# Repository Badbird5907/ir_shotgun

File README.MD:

# IR Shotgun
This is a IR shotgun (blaster) for the flipper zero that uses 8x APTD3216F3C-P22 infrared LEDs to absolutely FLOOD a room with infrared light.

## How does it work?
The flipper zero drives the A7 pin with PWM, which in turn drives the AO3400A MOSFET. The MOSFET then turns on and off the IR LEDs.

## How does this compare to the Rabbit Labs IR Blaster?
This blaster is (I think) a bit more powerful, and more directional compared to the Rabbit Labs IR Blaster.

## Design choices
- Instead of using 1x3 pin headers, I used 2x3 headers to provide better structural support for the blaster PCB.
- I used the AO3400A MOSFET over the 2N7000 because it's able to handle more current.
- My calculations for the resistor values for the LEDs (70 ohm -> 68 ohm) were based on the DC Forward Current of 50mA and not the peak forward current of 1200mA.

## Pictures

## BOM
|Name                                                                                                                       |Qty   |Price Per (USD)|Total (USD)|Link                                                                                       |
|---------------------------------------------------------------------------------------------------------------------------|------|---------------|-----------|-------------------------------------------------------------------------------------------|
|90 Degree header                                                                                                           |1     |$0.67          |$0.67      |https://www.digikey.ca/en/products/detail/w%C3%BCrth-elektronik/61300621021/4846834        |
|0.1uF 0805 cap                                                                                                             |1     |$0.08          |$0.08      |https://www.digikey.ca/en/products/detail/samsung-electro-mechanics/CL21B104KBCNNNC/3886661|
|10uF 1206 cap                                                                                                              |1     |$0.08          |$0.08      |https://www.digikey.ca/en/products/detail/samsung-electro-mechanics/CL31B106KAHNNNE/3887462|
|IR LED                                                                                                                     |8     |$0.52          |$4.16      |https://www.digikey.ca/en/products/detail/kingbright/APTD3216F3C-P22/8591562               |
|AO3400A MOSFET                                                                                                             |1     |$0.46          |$0.46      |https://www.digikey.ca/en/products/detail/alpha-omega-semiconductor-inc/AO3400A/1855772    |
|68 ohm res                                                                                                                 |4     |$0.60          |$2.40      |https://www.digikey.ca/en/products/detail/susumu/HRG3216P-68R0-D-T1/5762544                |
|10k res                                                                                                                    |1     |$0.10          |$0.10      |https://www.digikey.ca/en/products/detail/stackpole-electronics-inc/RMCF0805FT10K0/1760676 |
|15mm pin headers                                                                                                           |1     |$3.43          |$3.43      |https://www.aliexpress.com/item/1005006783391171.html                                      |
|Blaster PCB (JLC, LeadFree HASL)                                                                                           |1     |$5.20          |$5.20      |                                                                                           |
|Base PCB (JLC, LeadFree HASL)                                                                                              |1     |$5.20          |$5.20      |                                                                                           |
|TOTAL                                                                                                                      |      |               |$21.78     |                                                                                           |
|NOTE: Most of the resistors/caps here cost more in packages of one than in packages of 10+, I'd suggest ordering 10 of each|      |               |           |                                                                                           |
|                                                                                                                           |      |               |           |                                                                                           |
|                                                                                                                           |USD   |               |           |                                                                                           |
|JLC - DHL                                                                                                                  |$17.50|               |           |                                                                                           |
|DigiKey                                                                                                                    |$5.84 |               |           |                                                                                           |
|                                                                                                                           |      |               |           |                                                                                           |
|                                                                                                                           |      |               |           |                                                                                           |
|Grand Total                                                                                                                |      |               |$45.12     |                                                                                           |
                                                                                  |      |               |           |                                                                                           |
|Shipping

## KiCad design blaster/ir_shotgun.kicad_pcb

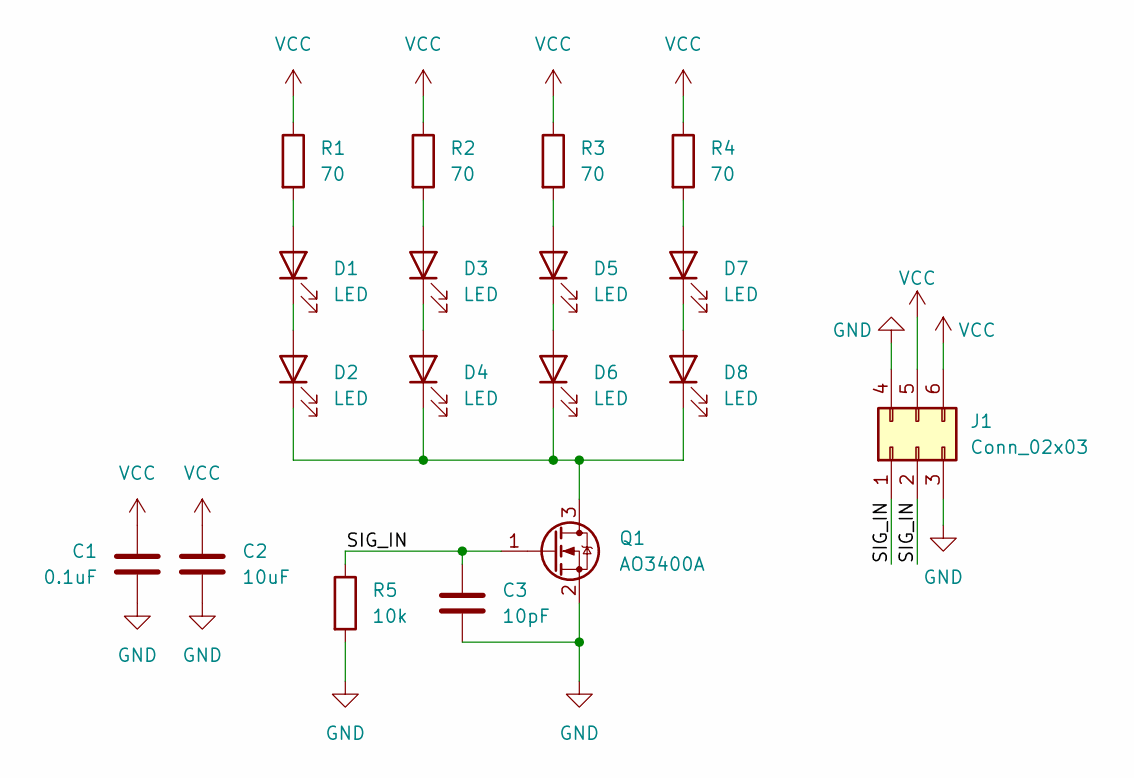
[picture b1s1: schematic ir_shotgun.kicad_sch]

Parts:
C1: 0.1uF; C_0805_2012Metric
C2: 10uF; C_1206_3216Metric
C3: 10pF; C_0805_2012Metric
D1, D2, D3, D4, D5, D6, D7, D8: LED; LED_1206_3216Metric
J1: Conn_02x03; PinHeader_2x03_P2.54mm_Vertical
Q1: AO3400A; SOT-23
R1, R2, R3, R4: 70; LED_1206_3216Metric
R5: 10k; R_0805_2012Metric

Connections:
/SIG_IN: C3.1, J1.1, J1.2, Q1.1 (G), R5.1
GND: C1.2, C2.2, C3.2, J1.3, J1.4, Q1.2 (S), R5.2
unnamed: D1.2 (A), R1.2
unnamed: D1.1 (K), D2.2 (A)
unnamed: D2.1 (K), D4.1 (K), D6.1 (K), D8.1 (K), Q1.3 (D)
unnamed: D3.2 (A), R2.2
unnamed: D3.1 (K), D4.2 (A)
unnamed: D5.2 (A), R3.2
unnamed: D5.1 (K), D6.2 (A)
unnamed: D7.2 (A), R4.2
unnamed: D7.1 (K), D8.2 (A)
VCC: C1.1, C2.1, J1.5, J1.6, R1.1, R2.1, R3.1, R4.1

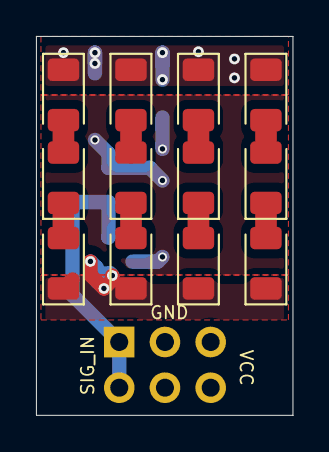
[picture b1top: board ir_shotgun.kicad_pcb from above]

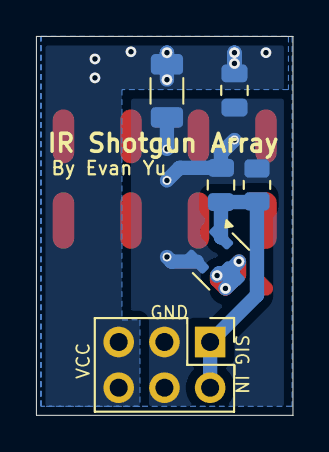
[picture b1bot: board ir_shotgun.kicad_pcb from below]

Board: 2 copper layers, 14.2 x 21.0 mm, 18 parts (6 on the bottom side), 12 nets.

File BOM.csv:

Name,Qty,Price Per (USD),Total (USD),Link
90 Degree header,1,$0.67,$0.67,https://www.digikey.ca/en/products/detail/w%C3%BCrth-elektro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
0.1uF 0805 cap,1,$0.08,$0.08,https://www.digikey.ca/en/products/detail/samsung-electro-me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
10uF 1206 cap,1,$0.08,$0.08,https://www.digikey.ca/en/products/detail/samsung-electro-me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
IR LED,8,$0.52,$4.16,https://www.digikey.ca/en/products/detail/kingbright/APTD321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
AO3400A MOSFET,1,$0.46,$0.46,https://www.digikey.ca/en/products/detail/alpha-omega-semico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
68 ohm res,4,$0.60,$2.40,https://www.digikey.ca/en/products/detail/susumu/HRG3216P-68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
10k res,1,$0.10,$0.10,https://www.digikey.ca/en/products/detail/stackpole-electron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
15mm pin headers,1,$3.43,$3.43,https://www.aliexpress.com/item/1005006783391171.html
"Blaster PCB (JLC, LeadFree HASL)",1,$5.20,$5.20,
"Base PCB (JLC, LeadFree HASL)",1,$5.20,$5.20,
TOTAL,,,$21.78,
"NOTE: Most of the resistors/caps here cost more in packages of one than in packages of 10+, I'd suggest ordering 10 of each",,,,
,,,,
,,,,
Shipping,USD,,,
JLC - DHL,$17.50,,,
DigiKey,$5.84,,,
,,,,
,,,,
Grand Total,,,$45.12,

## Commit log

2025-07-28 everything else
2025-07-28 case
